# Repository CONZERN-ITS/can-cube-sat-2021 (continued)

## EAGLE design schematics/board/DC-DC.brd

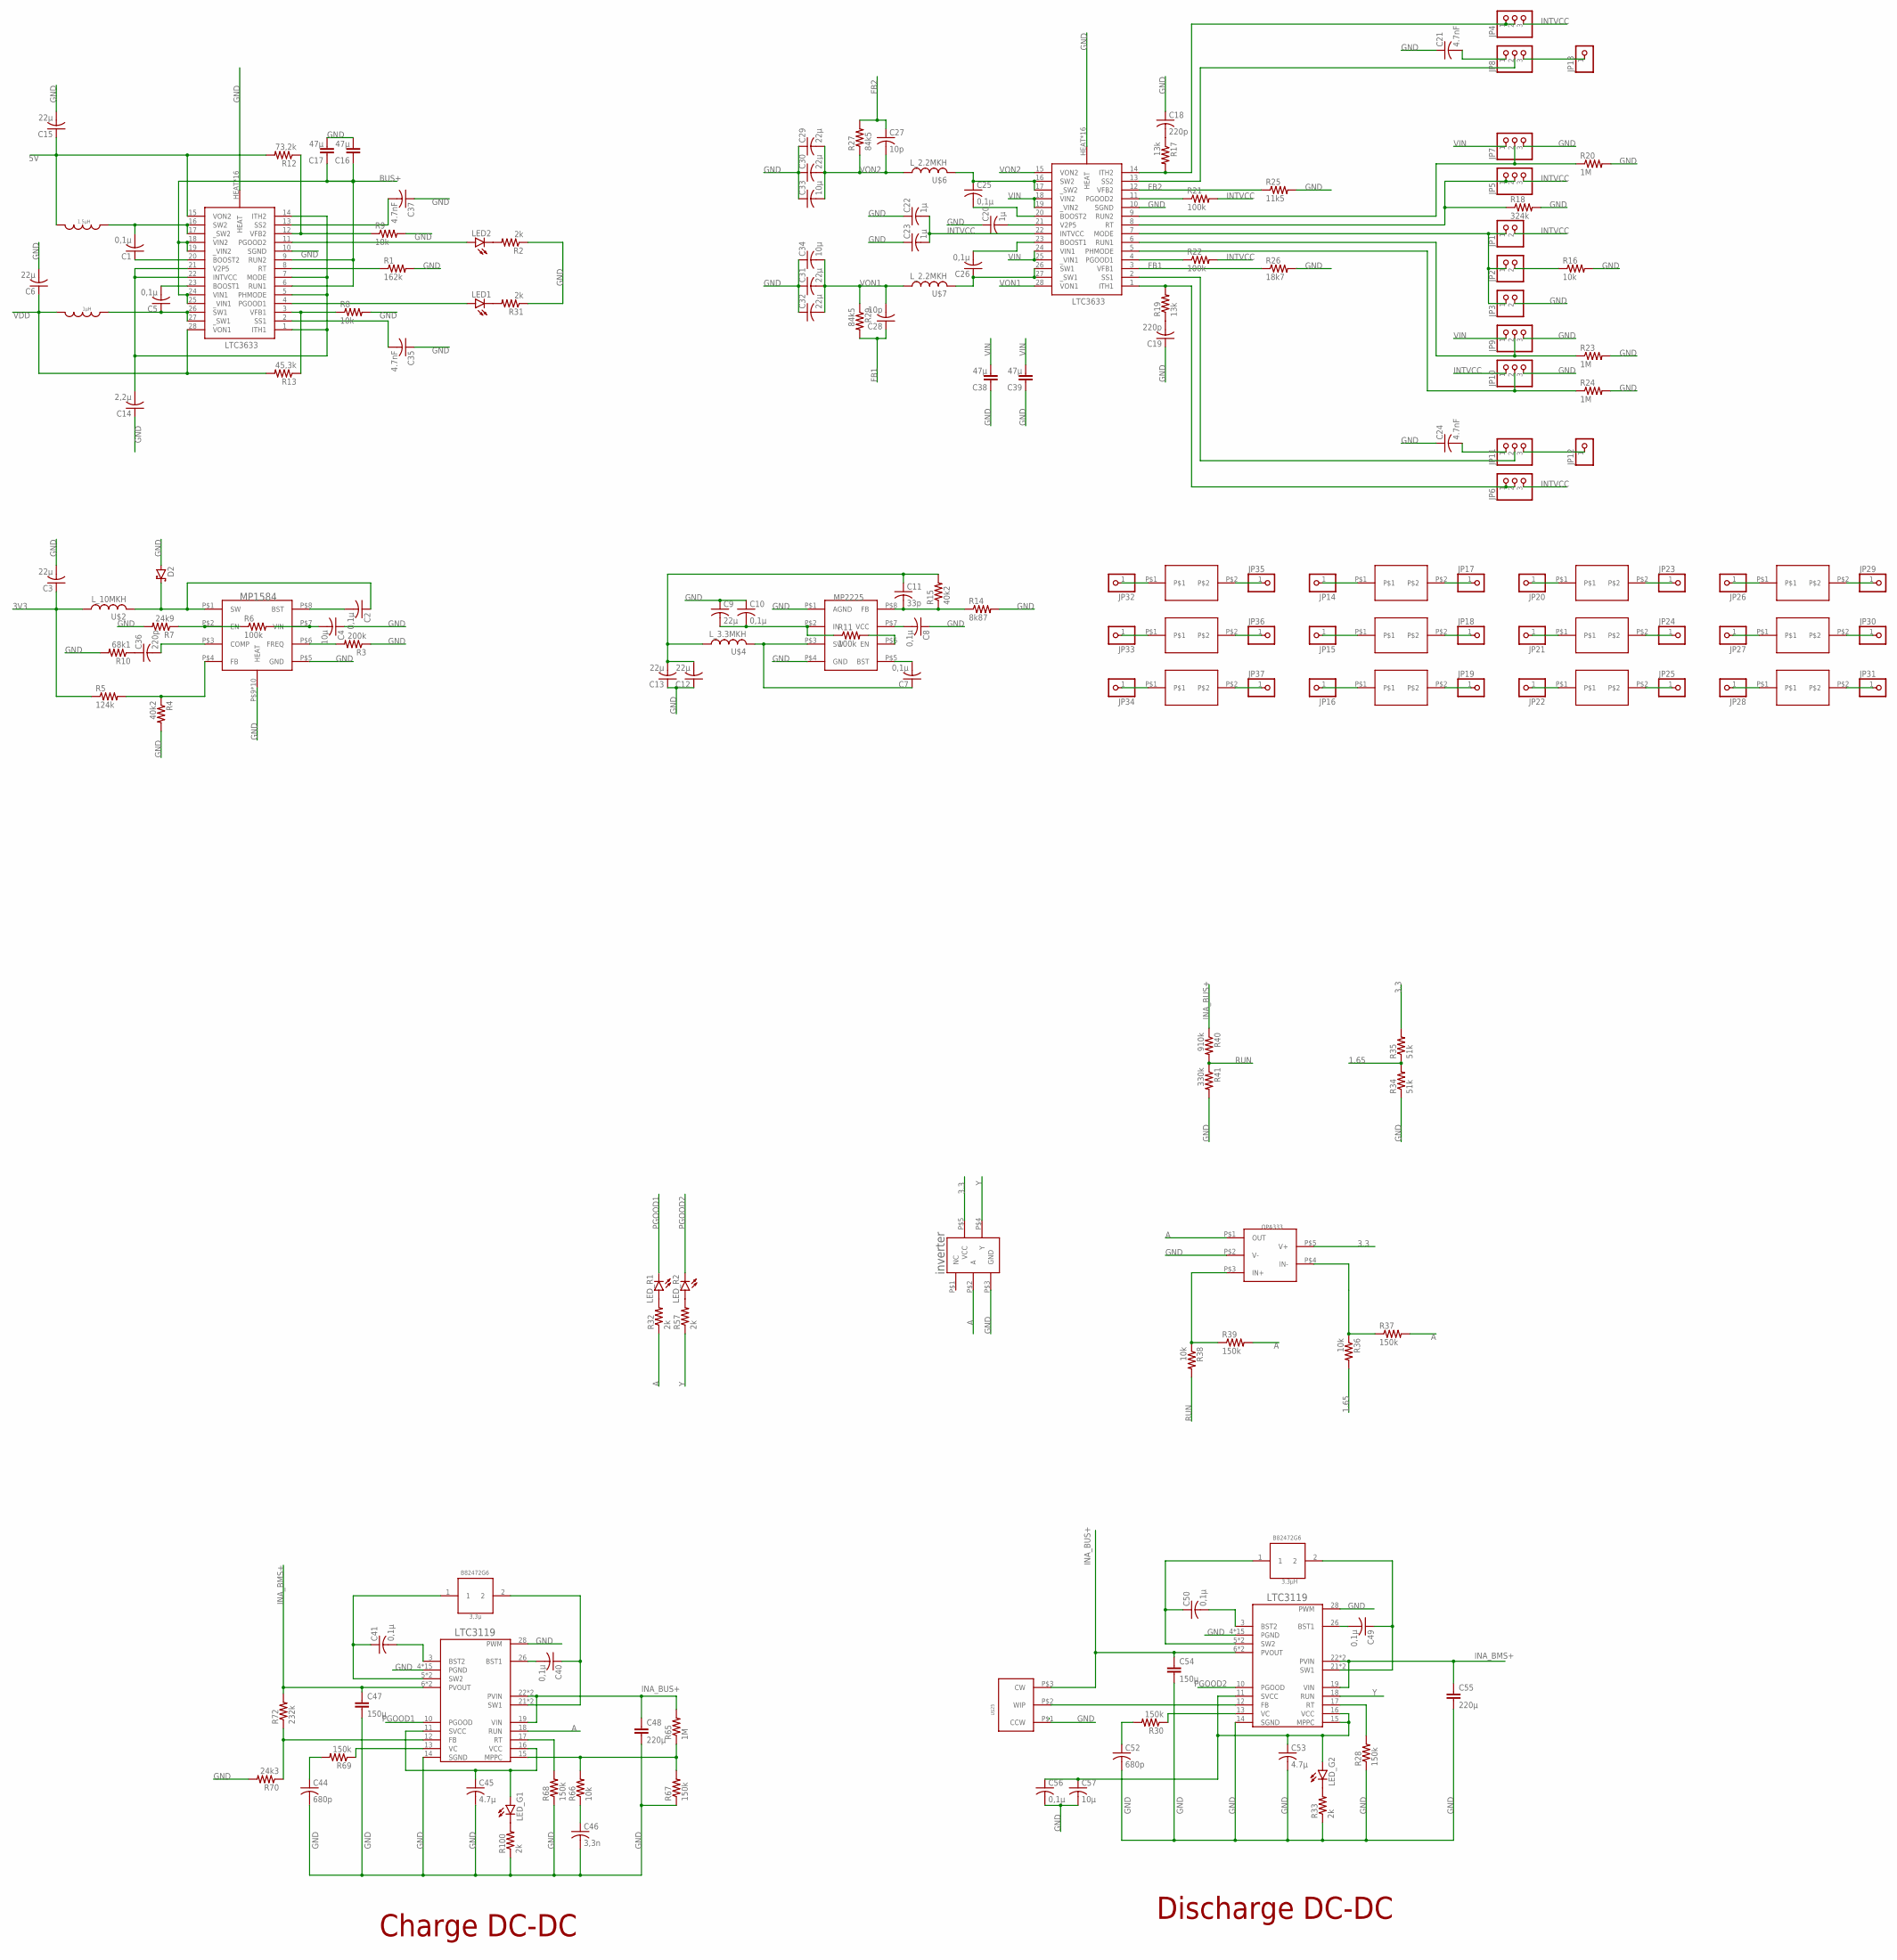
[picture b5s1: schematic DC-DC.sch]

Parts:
3,3µH: 3,3µ; B82472G6
3,3µH1: 3,3µH; B82472G6
C1, C2, C5, C7, C8, C10, C25, C26, C40, C41, C49, C50, C56: 0,1µ; C0603
C3, C6, C9, C12, C13, C15, C29, C30, C31, C32: 22µ; C1206
C4, C33, C34, C57: 10µ; C1206
C11: 33p; C0603
C14: 2,2µ; C0603
C16, C17, C38, C39: 47µ; C1210
C18, C19, C36: 220p; C0603
C20, C22, C23: 1µ; C0603
C21, C24, C35, C37: 4.7nF; C0603
C27, C28: 10p; C0603
C44, C52: 680p; C0603
C45, C53: 4.7µ; C1206
C46: 3,3n; C0603
C47, C54: 150µ; ECAP150
C48, C55: 220µ; ECAP220
D2: SCHOTTKY-DIODESMC; SMC
INVERT: INVERTER; SOT23-5
JP1, JP2, JP3: PINHD-1X2; 1X02
JP4, JP5, JP6, JP7, JP8, JP9, JP10, JP11: PINHD-1X3; 1X03
JP12, JP13, JP14, JP15, JP16, JP17, JP18, JP19, JP20, JP21, JP22, JP23, JP24, JP25, JP26, JP27, JP28, JP29, JP30, JP31, JP32, JP33, JP34, JP35, JP36, JP37: PINHD-1X1; 1X01
LED1, LED2: LEDCHIPLED_0603; CHIPLED_0603
LED_G1, LED_G2: LEDCHIPLED_0603; CHIPLED_0603
LED_R1, LED_R2: LEDCHIPLED_0603; CHIPLED_0603
OPA: OPA333; SOT23-5
R1: 162k; R0603
R2, R31, R32, R33, R57, R100: 2k; R0603
R3: 200k; R0603
R4, R15: 40k2; R0603
R5: 124k; R0603
R6, R11, R21, R22: 100k; R0603
R7: 24k9; R0603
R8, R9, R16, R36, R38, R66: 10k; R0603
R10: 68k1; R0603
R12: 73,2k; R0603
R13: 45,3k; R0603
R14: 8k87; R0603
R17, R19: 13k; R0603
R18: 324k; R0603
R20, R23, R24, R65: 1M; R0603
R25: 11k5; R0603
R26: 18k7; R0603
R27, R29: 84k5; R0603
R28, R30, R37, R39, R67, R68, R69: 150k; R0603
R34, R35: 51k; R0603
R40: 910k; R0603
R41: 330k; R0603
R70: 24k3; R0603
R72: 232k; R0603
U$1: MP1584+VIA
U$2: L_10MKH; L_12X12
U$3: MP2225; TSOT23-8
U$4: L_3.3MKH; L_SPM5020
U$5, U$10: LTC3633+VIA
U$6, U$7: L_2.2MKH; L_SPM4020
U$8: GRAFITGRAFIT1; GRAFIT1
U$9: GRAFITGRAFIT1_1; GRAFIT1_1
U$11: 1µH; VLS3012HBX
U$12: SPM4020
U$13: GRAFITGRAFIT1_2; GRAFIT1_2
U$14: GRAFITGRAFIT2; GRAFIT2
U$15: GRAFITGRAFIT2_1; GRAFIT2_1
U$16: GRAFITGRAFIT2_2; GRAFIT2_2
U$17: GRAFITGRAFIT3; GRAFIT3
U$18: GRAFITGRAFIT3_1; GRAFIT3_1
U$19: GRAFITGRAFIT3_2; GRAFIT3_2
U$20: GRAFITGRAFIT4; GRAFIT4
U$21: GRAFITGRAFIT4_1; GRAFIT4_1
U$22: GRAFITGRAFIT4_2; GRAFIT4_2
U$23, U$59: LTC31191; LTC3119+VIA
U$25: 32961; 3296W

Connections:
1.65: R34.2, R35.1, R36.2
3.3: INVERT.P$5 (VCC), OPA.P$5 (V+), R35.2
3V3: C3.1, R5.1, U$2.P$1 (1)
5V: C15.1, R12.2, U$10.15 (VON2), U$12.P$2 (2)
90: R65.1, R66.2, R67.2, U$59.15 (MPPC)
A: INVERT.P$2 (A), OPA.P$1 (OUT), R32.1, R37.2, R39.2, U$59.18 (RUN)
BUS+: C16.1, C17.1, U$10.6 (RUN1), U$10.9 (RUN2), U$10.18 (VIN2), U$10.19 (_VIN2), U$10.24 (VIN1), U$10.25 (_VIN1)
FB1: C28.1, R26.1, R29.2, U$5.3 (VFB1)
FB2: C27.1, R25.1, R27.2, U$5.12 (VFB2)
GND: C3.2, C4.1, C6.2, C8.1, C9.1, C10.1, C12.1, C13.1, C14.1, C15.2, C16.2, C17.2, C18.1, C19.1, C20.1, C21.1, C22.1, C23.1, C24.1, C29.1, C30.1, C31.1, C32.1, C33.1, C34.1, C35.1, C37.1, C38.1, C39.1, C44.2, C45.2, C46.2, C47.P$2 (2), C48.P$2 (2), C52.2, C53.2, C54.P$2 (2), C55.P$2 (2), C56.2, C57.2, D2.A, INVERT.P$3 (GND), JP3.2, JP7.3, JP9.3, JP10.3, OPA.P$2 (V-), R1.2, R2.1, R3.1, R4.2, R7.2, R8.2, R9.2, R10.2, R14.2, R16.2, R18.2, R20.2, R23.2, R24.2, R25.2, R26.2, R28.1, R31.1, R33.1, R34.1, R41.2, R67.1, R68.1, R70.2, R100.1, U$1.P$5 (GND), U$1.P$9 (HEAT), U$1.P$10 (HEAT), U$1.P$11 (HEAT), U$1.P$12 (HEAT), U$1.P$13 (HEAT), U$1.P$14 (HEAT), U$1.P$15 (HEAT), U$1.P$16 (HEAT), U$1.P$17 (HEAT), U$1.P$18 (HEAT), U$3.P$1 (AGND), U$3.P$4 (GND), U$5.10 (SGND), U$5.HEAT, U$5.P$1 (HEAT), U$5.P$2 (HEAT), U$5.P$3 (HEAT), U$5.P$4 (HEAT), U$5.P$5 (HEAT), U$5.P$6 (HEAT), U$5.P$7 (HEAT), U$5.P$8 (HEAT), U$5.P$9 (HEAT), U$5.P$10 (HEAT), U$5.P$11 (HEAT), U$5.P$12 (HEAT), U$5.P$13 (HEAT), U$5.P$14 (HEAT), U$5.P$15 (HEAT), U$10.10 (SGND), U$10.HEAT, U$10.P$1 (HEAT), U$10.P$2 (HEAT), U$10.P$3 (HEAT), U$10.P$4 (HEAT), U$10.P$5 (HEAT), U$10.P$6 (HEAT), U$10.P$7 (HEAT), U$10.P$8 (HEAT), U$10.P$9 (HEAT), U$10.P$10 (HEAT), U$10.P$11 (HEAT), U$10.P$12 (HEAT), U$10.P$13 (HEAT), U$10.P$14 (HEAT), U$10.P$15 (HEAT), U$23.4 (PGND), U$23.9 (PGND), U$23.14 (SGND), U$23.20 (PGND), U$23.25 (PGND), U$23.28 (PWM), U$23.29 (PGND), U$23.P$1 (PGND), U$23.P$2 (PGND), U$23.P$3 (PGND), U$23.P$4 (PGND), U$23.P$5 (PGND), U$23.P$6 (PGND), U$23.P$7 (PGND), U$23.P$8 (PGND), U$23.P$9 (PGND), U$23.P$10 (PGND), U$25.P$1 (CCW), U$59.4 (PGND), U$59.9 (PGND), U$59.14 (SGND), U$59.20 (PGND), U$59.25 (PGND), U$59.28 (PWM), U$59.29 (PGND), U$59.P$1 (PGND), U$59.P$2 (PGND), U$59.P$3 (PGND), U$59.P$4 (PGND), U$59.P$5 (PGND), U$59.P$6 (PGND), U$59.P$7 (PGND), U$59.P$8 (PGND), U$59.P$9 (PGND), U$59.P$10 (PGND)
INA_BMS+: C47.P$1 (1), C55.P$1 (1), R72.2, U$23.19 (VIN), U$23.22 (PVIN), U$23.23 (PVIN), U$59.6 (PVOUT), U$59.7 (PVOUT)
INA_BUS+: C48.P$1 (1), C54.P$1 (1), R40.1, R65.2, U$23.6 (PVOUT), U$23.7 (PVOUT), U$25.P$3 (CW), U$59.19 (VIN), U$59.22 (PVIN), U$59.23 (PVIN)
INTVCC: C22.2, C23.2, JP1.2, JP4.3, JP5.3, JP6.3, JP10.1, R21.2, R22.2, U$5.22 (INTVCC)
unnamed: R1.1, U$10.8 (RT)
unnamed: LED1.C, R31.2
unnamed: LED2.A, U$10.11 (PGOOD2)
unnamed: LED2.C, R2.2
unnamed: C2.2, U$1.P$8 (BST)
unnamed: C2.1, D2.C, U$1.P$1 (SW), U$2.P$2 (2)
unnamed: R3.2, U$1.P$6 (FREQ)
unnamed: R4.1, R5.2, U$1.P$4 (FB)
unnamed: R6.1, R7.1, U$1.P$2 (EN)
unnamed: C4.2, R6.2, U$1.P$7 (VIN)
unnamed: C36.1, R10.1
unnamed: C36.2, U$1.P$3 (COMP)
unnamed: C7.2, U$3.P$5 (BST)
unnamed: C7.1, U$3.P$3 (SW), U$4.P$2 (2)
unnamed: R11.2, U$3.P$6 (EN)
unnamed: C8.2, U$3.P$7 (VCC)
unnamed: C9.2, C10.2, R11.1, U$3.P$2 (IN)
unnamed: C11.2, R14.1, R15.1, U$3.P$8 (FB)
unnamed: C11.1, C12.2, C13.2, R15.2, U$4.P$1 (1)
unnamed: JP1.1, JP2.1, JP3.1, U$5.7 (MODE)
unnamed: JP4.1, JP4.2, R17.2, U$5.14 (ITH2)
unnamed: C18.2, R17.1
unnamed: JP2.2, R16.1
unnamed: C14.2, U$10.1 (ITH1), U$10.5 (PHMODE), U$10.7 (MODE), U$10.14 (ITH2), U$10.21 (V2P5), U$10.22 (INTVCC)
unnamed: R8.1, R13.1, U$10.3 (VFB1)
unnamed: JP5.1, JP5.2, R18.1, U$5.8 (RT)
unnamed: C20.2, U$5.21 (V2P5)
unnamed: C5.1, U$10.26 (SW1), U$10.27 (_SW1), U$11.P$1 (1)
unnamed: JP6.1, JP6.2, R19.2, U$5.1 (ITH1)
unnamed: C19.2, R19.1
unnamed: C5.2, U$10.23 (BOOST1)
unnamed: C1.1, U$10.20 (BOOST2)
unnamed: C1.2, U$10.16 (SW2), U$10.17 (_SW2), U$12.P$1 (1)
unnamed: C25.1, U$5.16 (SW2), U$5.17 (_SW2), U$6.P$2 (2)
unnamed: C26.1, U$5.26 (SW1), U$5.27 (_SW1), U$7.P$2 (2)
unnamed: R22.1, U$5.4 (PGOOD1)
unnamed: JP8.2, U$5.13 (SS2)
unnamed: JP7.2, R20.1, U$5.9 (RUN2)
unnamed: R9.1, R12.1, U$10.12 (VFB2)
unnamed: R21.1, U$5.11 (PGOOD2)
unnamed: JP9.2, R23.1, U$5.6 (RUN1)
unnamed: JP11.2, U$5.2 (SS1)
unnamed: C21.2, JP8.1
unnamed: JP10.2, R24.1, U$5.5 (PHMODE)
unnamed: C24.2, JP11.1
unnamed: C25.2, U$5.20 (BOOST2)
unnamed: LED1.A, U$10.4 (PGOOD1)
unnamed: C26.2, U$5.23 (BOOST1)
unnamed: JP8.3, JP13.1
unnamed: JP11.3, JP12.1
unnamed: C35.2, U$10.2 (SS1)
unnamed: C37.2, U$10.13 (SS2)
unnamed: JP14.1, U$14.P$1
unnamed: JP15.1, U$15.P$1
unnamed: JP16.1, U$16.P$1
unnamed: JP17.1, U$14.P$2
unnamed: JP18.1, U$15.P$2
unnamed: JP19.1, U$16.P$2
unnamed: JP20.1, U$17.P$1
unnamed: JP21.1, U$18.P$1
unnamed: JP22.1, U$19.P$1
unnamed: JP23.1, U$17.P$2
unnamed: JP24.1, U$18.P$2
unnamed: JP25.1, U$19.P$2
unnamed: JP26.1, U$20.P$1
unnamed: JP27.1, U$21.P$1
unnamed: JP28.1, U$22.P$1
unnamed: JP29.1, U$20.P$2
unnamed: JP30.1, U$21.P$2
unnamed: JP31.1, U$22.P$2
unnamed: JP32.1, U$8.P$1
unnamed: JP33.1, U$9.P$1
unnamed: JP34.1, U$13.P$1
unnamed: JP35.1, U$8.P$2
unnamed: JP36.1, U$9.P$2
unnamed: JP37.1, U$13.P$2
unnamed: 3,3µH1.2, C49.1, U$23.21 (SW1), U$23.24 (SW1)
unnamed: 3,3µH1.1, C50.1, U$23.5 (SW2), U$23.8 (SW2)
unnamed: R28.2, U$23.17 (RT)
unnamed: C49.2, U$23.26 (BST1)
unnamed: R30.1, U$23.13 (VC)
unnamed: C52.1, R30.2
unnamed: C50.2, U$23.3 (BST2)
unnamed: LED_R1.A, R32.2
unnamed: U$23.12 (FB), U$25.P$2 (WIP)
unnamed: LED_R2.A, R57.2
unnamed: R70.1, R72.1, U$59.12 (FB)
unnamed: OPA.P$3 (IN+), R38.1, R39.1
unnamed: LED_G1.C, R100.2
unnamed: LED_G2.C, R33.2
unnamed: C41.2, U$59.3 (BST2)
unnamed: 3,3µH.2, C40.1, U$59.21 (SW1), U$59.24 (SW1)
unnamed: 3,3µH.1, C41.1, U$59.5 (SW2), U$59.8 (SW2)
unnamed: R69.1, U$59.13 (VC)
unnamed: C44.1, R69.2
unnamed: C46.1, R66.1
unnamed: R68.2, U$59.17 (RT)
unnamed: C40.2, U$59.26 (BST1)
unnamed: C53.1, C56.1, C57.1, LED_G2.A, U$23.11 (SVCC), U$23.15 (MPPC), U$23.16 (VCC)
unnamed: C45.1, LED_G1.A, U$59.11 (SVCC), U$59.16 (VCC)
unnamed: OPA.P$4 (IN-), R36.1, R37.1
PGOOD1: LED_R1.C, U$59.10 (PGOOD)
PGOOD2: LED_R2.C, U$23.10 (PGOOD)
RUN: R38.2, R40.2, R41.1
VDD: C6.1, R13.2, U$10.28 (VON1), U$11.P$2 (2)
VIN: C38.2, C39.2, JP7.1, JP9.1, U$5.18 (VIN2), U$5.19 (_VIN2), U$5.24 (VIN1), U$5.25 (_VIN1)
VON1: C28.2, C31.2, C32.2, C34.2, R29.1, U$5.28 (VON1), U$7.P$1 (1)
VON2: C27.2, C29.2, C30.2, C33.2, R27.1, U$5.15 (VON2), U$6.P$1 (1)
Y: INVERT.P$4 (Y), R57.1, U$23.18 (RUN)

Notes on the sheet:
1µH
1.5µH
Charge DC-DC
Discharge DC-DC

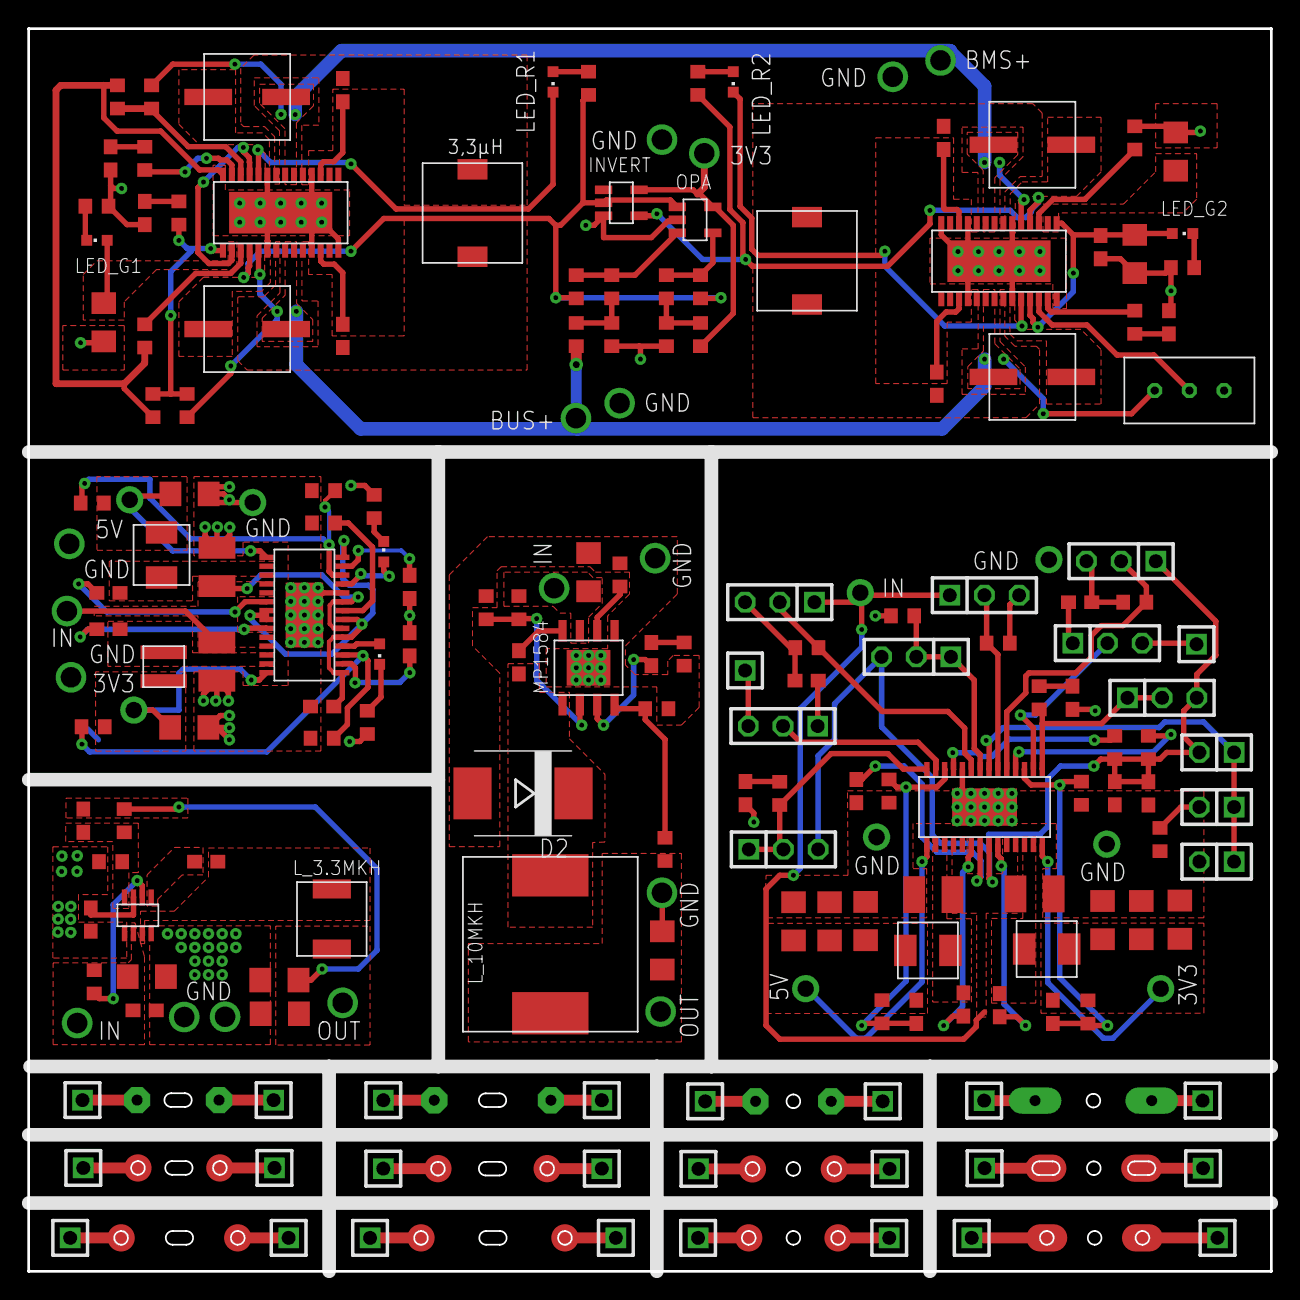
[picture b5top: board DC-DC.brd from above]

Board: 2 copper layers, 91.0 x 91.0 mm, 177 parts (0 on the bottom side), 122 nets.

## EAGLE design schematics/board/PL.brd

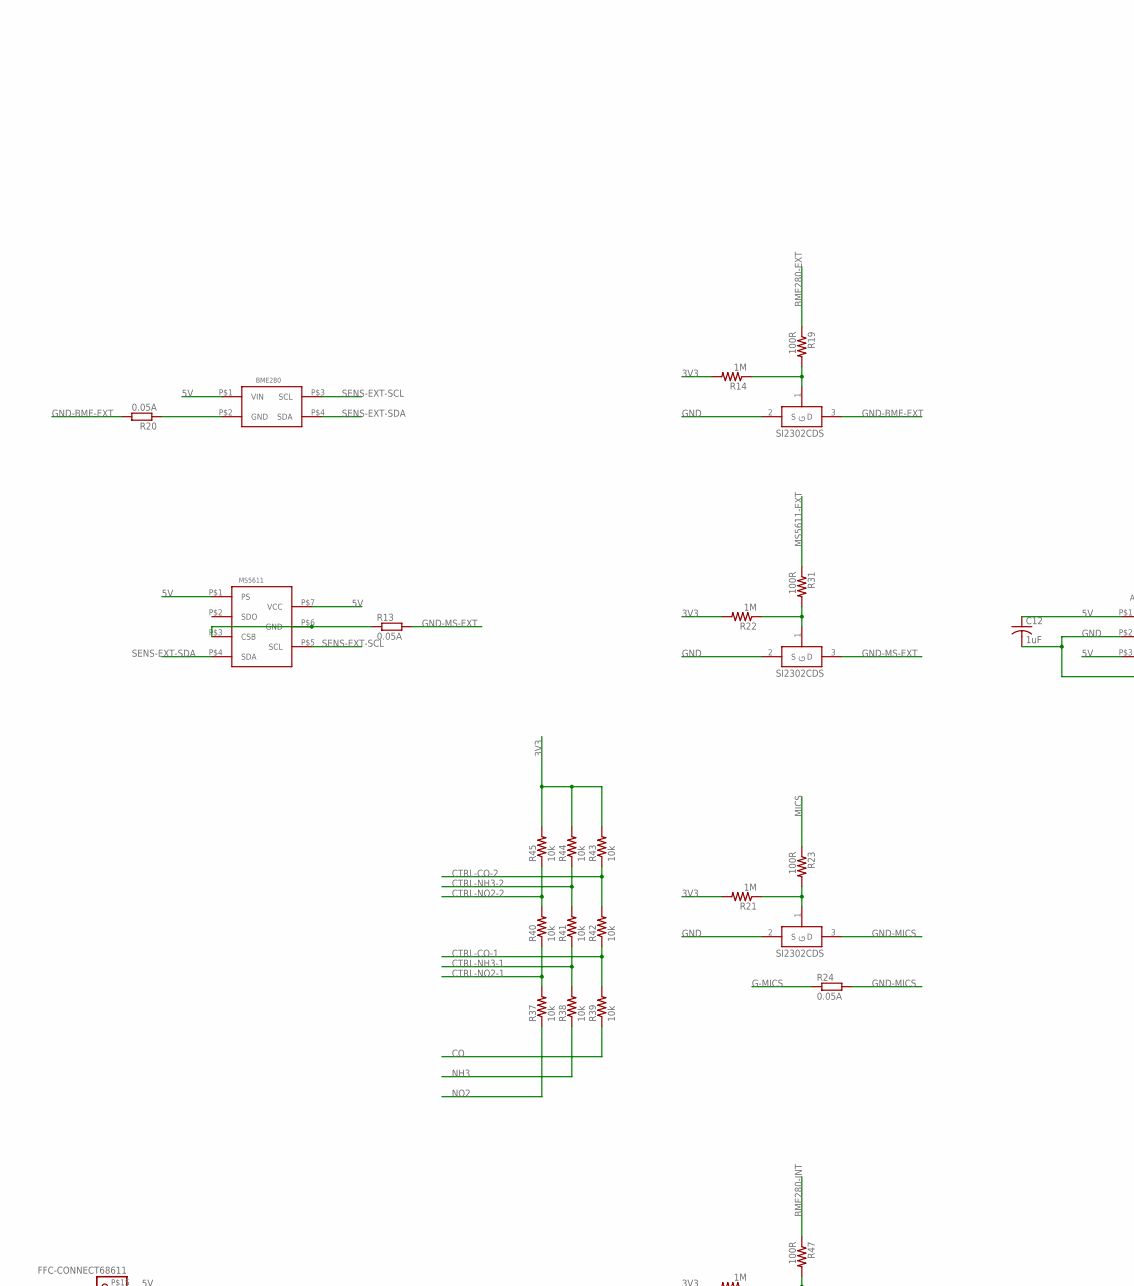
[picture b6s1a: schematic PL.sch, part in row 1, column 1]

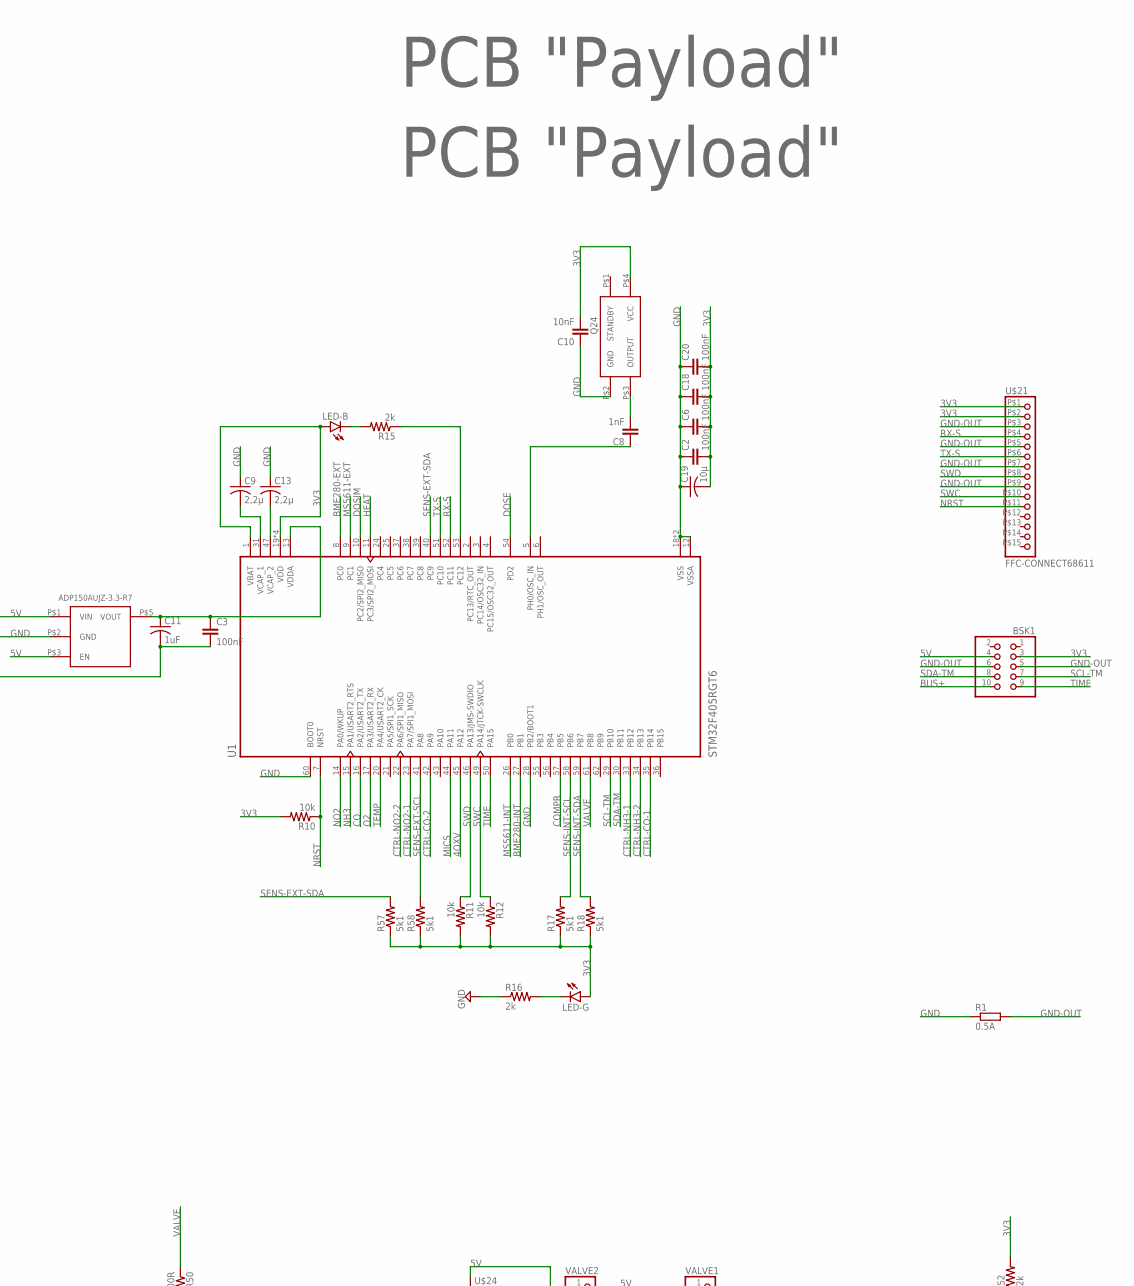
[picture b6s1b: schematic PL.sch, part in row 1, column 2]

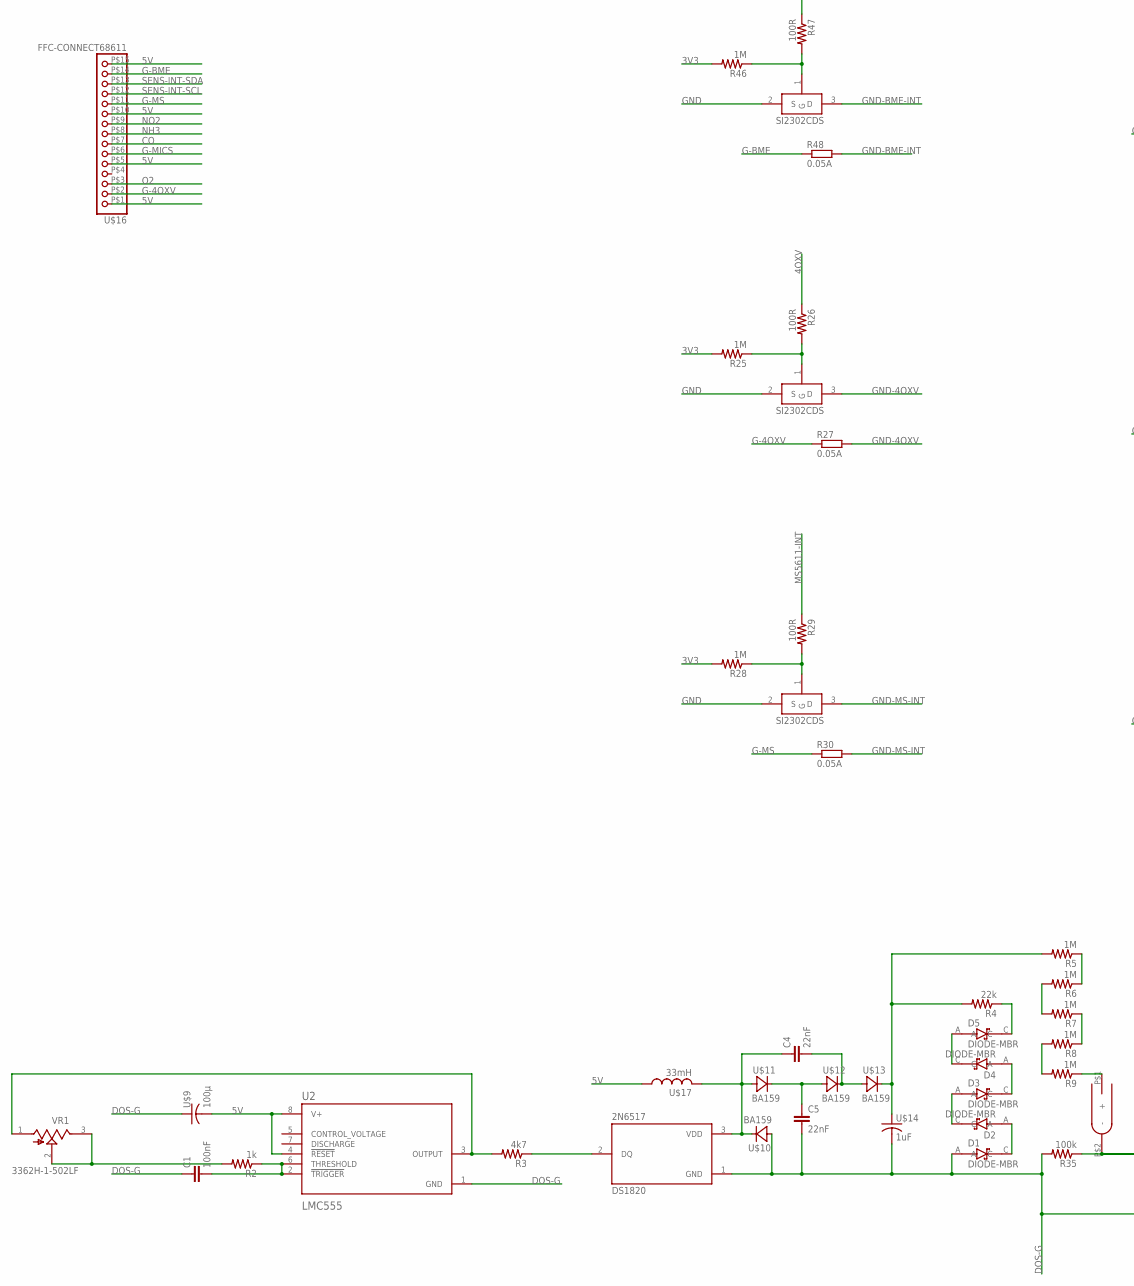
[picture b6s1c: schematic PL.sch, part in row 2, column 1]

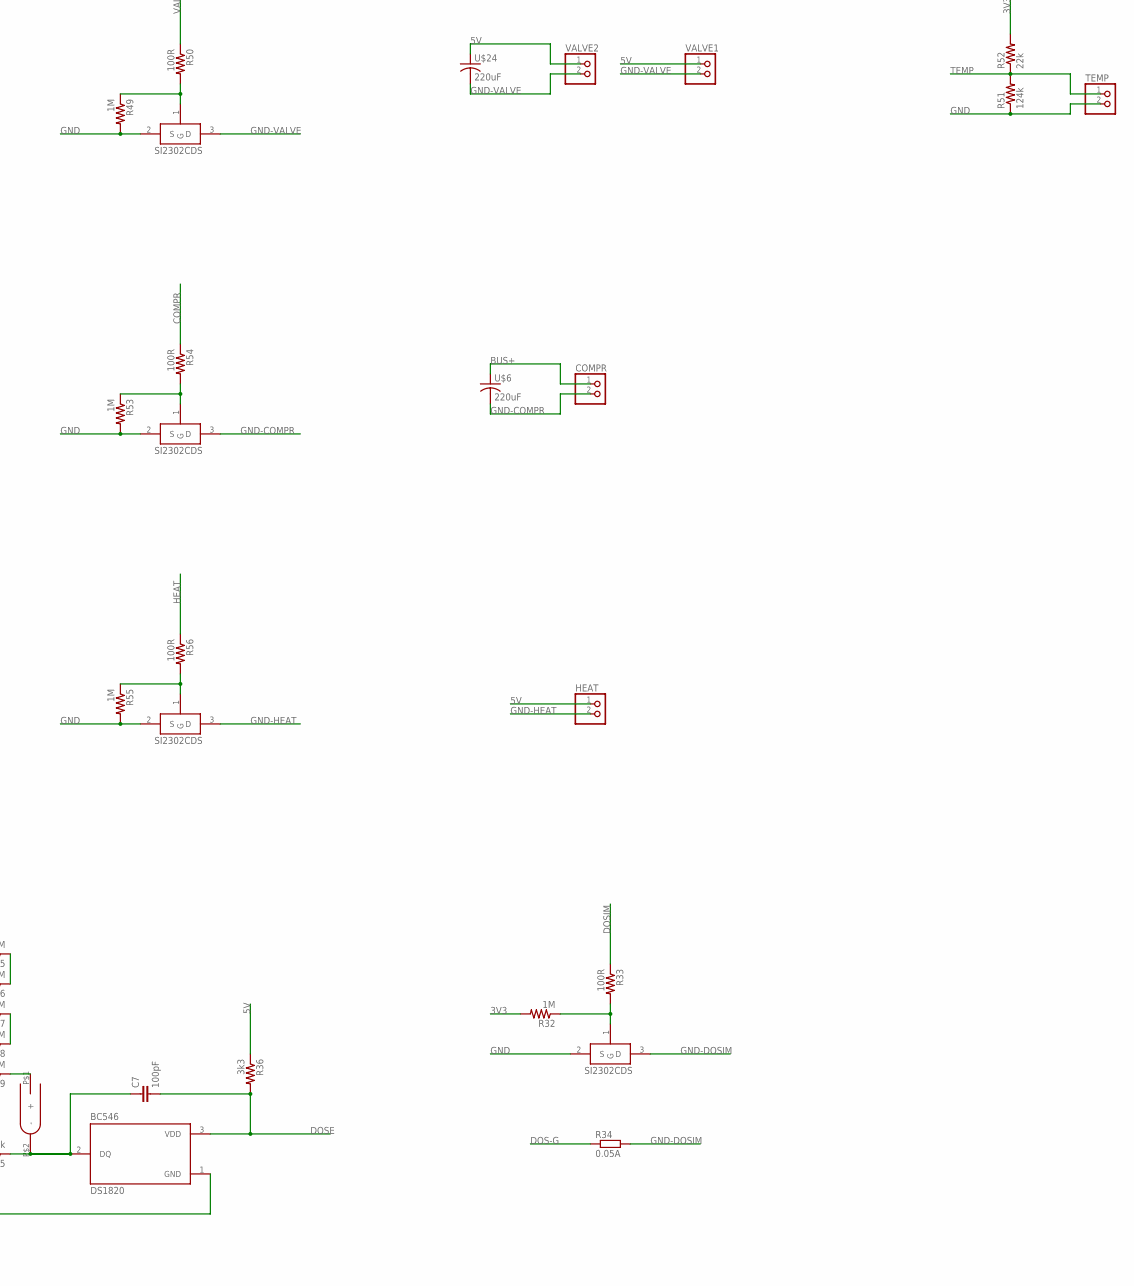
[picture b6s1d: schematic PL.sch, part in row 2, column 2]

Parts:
2N6517: DS1820; TO92/TO226
BC546: DS1820; TO92/TO226
BME280: BME280BME280-PINS-ONLY; BME280-PINS-ONLY
BSK1: PINHD-2X5; 2X05
C1, C2, C3, C6, C18, C20: 100nF; C0603
C4, C5: 22nF; C1210
C7: 100pF; C0603
C8: 1nF; C0603
C9, C13: 2,2µ; C0603
C10: 10nF; C0603
C11, C12: 1uF; ECAP-SMD-D4
C19: 10µ; C1206
COMPR: PINHD-1X2; 1X02
D1, D2, D3, D4, D5: DIODE-MBR; SOD123
HEAT: PINHD-1X2; 1X02
LED-B: LEDCHIPLED_0603; CHIPLED_0603
LED-G: LEDCHIPLED_0603; CHIPLED_0603
MS5611: MS5611MS5611-PIN-ONLY; MS5611-PINS-ONLY
Q24: Q24
R1: 0.5A; R1210
R2: 1k; R0603
R3: 4k7; R0603
R4, R52: 22k; R0603
R5, R6, R7, R8, R9, R14, R21, R22, R25, R28, R32, R46, R49, R53, R55: 1M; R0603
R10, R11, R12, R37, R38, R39, R40, R41, R42, R43, R44, R45: 10k; R0603
R13, R20, R24, R27, R30, R34, R48: 0.05A; R1210
R15, R16: 2k; R0603
R17, R18, R57, R58: 5k1; R0603
R19, R23, R26, R29, R31, R33, R47, R50, R54, R56: 100R; R0603
R35: 100k; R0603
R36: 3k3; R0603
R51: 124k; R0603
SI2302-0, SI2302-1, SI2302-2, SI2302-3, SI2302-4, SI2302-5, SI2302-6, SI2302-7, SI2302-8, SI2302-9: SI2302CDS; SOT23-3
STAB: ADP150AUJZ-3.3-R7; SOT23-5
TEMP: PINHD-1X2; 1X02
U1: STM32F405RGT6; QFP50P1200X1200X160-64N
U2: LMC555; SOIC127P599X175-8N
U$1, U$26: PCB "Payload"; ITS-LOGO
U$6, U$24: 220uF; ECAP220-CMD
U$9: 100µ; ECAP100-CMD
U$10, U$11, U$12, U$13: BA159
U$14: 1uF; ECAP1MK
U$15: DOSIM
U$16, U$21: FFC-CONNECT68611; 68611
U$17: 33mH; RCH114NP
VALVE1, VALVE2: PINHD-1X2; 1X02
VR1: 3362H-1-502LF; TRIM_3362H-1-502LF

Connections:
3V3: BSK1.3, C2.2, C6.2, C10.2, C18.2, C19.2, C20.2, LED-B.A, LED-G.A, Q24.P$4 (VCC), R10.2, R11.2, R12.2, R14.2, R17.1, R18.1, R21.2, R22.2, R25.2, R28.2, R32.2, R43.2, R44.2, R45.2, R46.2, R52.2, R57.1, R58.1, U1.1 (VBAT), U1.19 (VDD), U1.32 (VDD), U1.48 (VDD), U1.64 (VDD), U$21.P$1 (1), U$21.P$2 (2)
4OXV: R26.1, U1.45 (PA12)
5V: BME280.P$1 (VIN), BSK1.4, C12.P+ (1), HEAT.1, MS5611.P$1 (PS), MS5611.P$7 (VCC), R36.1, STAB.P$1 (VIN), STAB.P$3 (EN), U2.4 (!RESET!), U2.8 (V+), U$9.P$2 (2), U$16.P$1 (1), U$16.P$5 (5), U$16.P$10 (10), U$16.P$15 (15), U$17.P$1 (1), U$24.P$1 (1), VALVE1.1, VALVE2.1
BME280-EXT: R19.1, U1.8 (PC0)
BME280-INT: R47.1, U1.27 (PB1)
BUS+: BSK1.10, COMPR.1, U$6.P$1 (1)
CO: R39.1, U1.16 (PA2/USART2_TX), U$16.P$7 (7)
COMPR: R54.1, U1.57 (PB5)
CTRL-CO-1: R39.2, R42.1, U1.35 (PB14)
CTRL-CO-2: R42.2, R43.1, U1.42 (PA9)
CTRL-NH3-1: R38.2, R41.1, U1.33 (PB12)
CTRL-NH3-2: R41.2, R44.1, U1.34 (PB13)
CTRL-NO2-1: R37.2, R40.1, U1.23 (PA7/SPI1_MOSI)
CTRL-NO2-2: R40.2, R45.1, U1.22 (PA6/SPI1_MISO)
DOS-G: 2N6517.1 (GND), BC546.1 (GND), C1.1, C5.2, D1.A, R34.1, R35.2, U2.1 (GND), U$9.P$1 (1), U$10.P$1 (A), U$14.P$2 (2)
DOSE: BC546.3 (VDD), C7.2, R36.2, U1.54 (PD2)
DOSIM: R33.1, U1.10 (PC2/SPI2_MISO)
G-4OXV: R27.1, U$16.P$2 (2)
G-BME: R48.1, U$16.P$14 (14)
G-MICS: R24.1, U$16.P$6 (6)
G-MS: R30.1, U$16.P$11 (11)
GND: C2.1, C3.2, C6.1, C9.1, C10.1, C11.P- (2), C12.P- (2), C13.1, C18.1, C19.1, C20.1, Q24.P$2 (GND), R1.1, R16.1, R49.2, R51.1, R53.2, R55.2, SI2302-0.2 (S), SI2302-1.2 (S), SI2302-2.2 (S), SI2302-3.2 (S), SI2302-4.2 (S), SI2302-5.2 (S), SI2302-6.2 (S), SI2302-7.2 (S), SI2302-8.2 (S), SI2302-9.2 (S), STAB.P$2 (GND), TEMP.2, U1.12 (VSSA), U1.18 (VSS), U1.28 (PB2/BOOT1), U1.60 (BOOT0), U1.63 (VSS)
GND-4OXV: R27.2, SI2302-8.3 (D)
GND-BME-EXT: R20.2, SI2302-2.3 (D)
GND-BME-INT: R48.2, SI2302-5.3 (D)
GND-COMPR: COMPR.2, SI2302-9.3 (D), U$6.P$2 (2)
GND-DOSIM: R34.2, SI2302-4.3 (D)
GND-HEAT: HEAT.2, SI2302-3.3 (D)
GND-MICS: R24.2, SI2302-7.3 (D)
GND-MS-EXT: R13.2, SI2302-1.3 (D)
GND-MS-INT: R30.2, SI2302-6.3 (D)
GND-OUT: BSK1.5, BSK1.6, R1.2, U$21.P$3 (3), U$21.P$5 (5), U$21.P$7 (7), U$21.P$9 (9)
GND-VALVE: SI2302-0.3 (D), U$24.P$2 (2), VALVE1.2, VALVE2.2
HEAT: R56.1, U1.11 (PC3/SPI2_MOSI)
MICS: R23.1, U1.44 (PA11)
MS5611-EXT: R31.1, U1.9 (PC1)
MS5611-INT: R29.1, U1.26 (PB0)
unnamed: MS5611.P$3 (CSB), MS5611.P$6 (GND), R13.1
unnamed: R14.1, R19.2, SI2302-2.1 (G)
unnamed: BME280.P$2 (GND), R20.1
unnamed: C8.2, Q24.P$3 (OUTPUT)
unnamed: C8.1, U1.5 (PH0/OSC_IN)
unnamed: R21.1, R23.2, SI2302-7.1 (G)
unnamed: R49.1, R50.2, SI2302-0.1 (G)
unnamed: R25.1, R26.2, SI2302-8.1 (G)
unnamed: C3.1, C11.P+ (1), STAB.P$5 (VOUT), U1.13 (VDDA)
unnamed: R46.1, R47.2, SI2302-5.1 (G)
unnamed: R22.1, R31.2, SI2302-1.1 (G)
unnamed: R28.1, R29.2, SI2302-6.1 (G)
unnamed: LED-G.C, R16.2
unnamed: R32.1, R33.2, SI2302-4.1 (G)
unnamed: C1.2, R2.1, U2.2 (!TRIGGER!), U2.6 (THRESHOLD)
unnamed: R2.2, VR1.2 (WIPER), VR1.3 (CW)
unnamed: R3.2, U2.3 (OUTPUT), VR1.1 (CCW)
unnamed: 2N6517.2 (DQ), R3.1
unnamed: 2N6517.3 (VDD), C4.1, U$10.P$2 (C), U$11.P$1 (A), U$17.P$2 (2)
unnamed: C5.1, U$11.P$2 (C), U$12.P$1 (A)
unnamed: C4.2, U$12.P$2 (C), U$13.P$1 (A)
unnamed: R4.2, R5.2, U$13.P$2 (C), U$14.P$1 (1)
unnamed: D1.C, D2.A
unnamed: D2.C, D3.A
unnamed: D3.C, D4.A
unnamed: D4.C, D5.A
unnamed: D5.C, R4.1
unnamed: R5.1, R6.1
unnamed: C13.2, U1.47 (VCAP_2)
unnamed: R6.2, R7.2
unnamed: R7.1, R8.1
unnamed: R8.2, R9.2
unnamed: R9.1, U$15.P$1 (+)
unnamed: BC546.2 (DQ), C7.1, R35.1, U$15.P$2 (-)
unnamed: C9.2, U1.31 (VCAP_1)
unnamed: LED-B.C, R15.2
unnamed: R15.1, U1.53 (PC12)
unnamed: R53.1, R54.2, SI2302-9.1 (G)
unnamed: R55.1, R56.2, SI2302-3.1 (G)
NH3: R38.1, U1.15 (PA1/USART2_RTS), U$16.P$8 (8)
NO2: R37.1, U1.14 (PA0/WKUP), U$16.P$9 (9)
NRST: R10.1, U1.7 (NRST), U$21.P$11 (11)
O2: U1.17 (PA3/USART2_RX), U$16.P$3 (3)
RX-S: U1.52 (PC11), U$21.P$4 (4)
SCL-TM: BSK1.7, U1.29 (PB10)
SDA-TM: BSK1.8, U1.30 (PB11)
SENS-EXT-SCL: BME280.P$3 (SCL), MS5611.P$5 (SCL), R58.2, U1.41 (PA8)
SENS-EXT-SDA: BME280.P$4 (SDA), MS5611.P$4 (SDA), R57.2, U1.40 (PC9)
SENS-INT-SCL: R17.2, U1.58 (PB6), U$16.P$12 (12)
SENS-INT-SDA: R18.2, U1.59 (PB7), U$16.P$13 (13)
SWC: R12.1, U1.49 (PA14/JTCK-SWCLK), U$21.P$10 (10)
SWD: R11.1, U1.46 (PA13/JMS-SWDIO), U$21.P$8 (8)
TEMP: R51.2, R52.1, TEMP.1, U1.20 (PA4/USART2_CK)
TIME: BSK1.9, U1.50 (PA15)
TX-S: U1.51 (PC10), U$21.P$6 (6)
VALVE: R50.1, U1.61 (PB8)

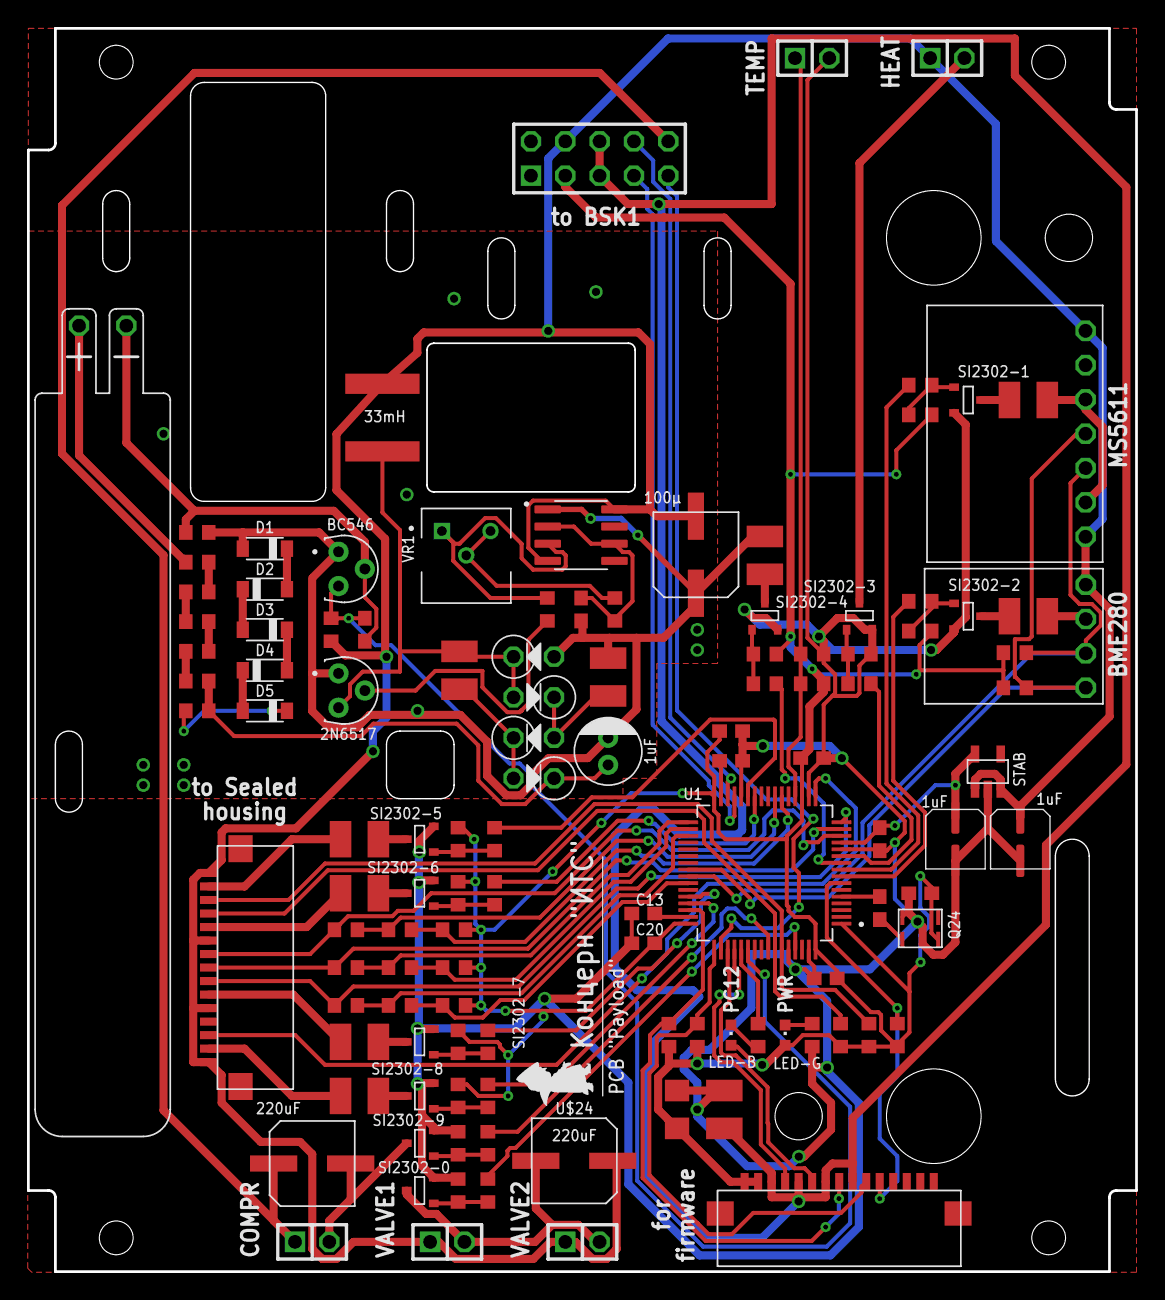
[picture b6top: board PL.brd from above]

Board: 2 copper layers, 82.0 x 92.0 mm, 120 parts (1 on the bottom side), 93 nets.
